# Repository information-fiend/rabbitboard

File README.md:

<h2 align="center">
 
 rabbitboard
</h2>
&nbsp;

> A 65% mechanical keyboard with a knob and screen. 

After making a macropad, holding it felt like *whoa* i wanna make more. Started designing back in March but finished it cuz of Highway! 

### 📷 Pictures

### BOM
|Qty| Device|	Link	|Cost	|
|---|-----|--------|-------|
65|	Through-hole 1N4148 Diodes	|[Link](https://www.aliexpress.us/item/3256807621334582.html?spm=a2g0o.productlist.main.1.50f12c82bUE2UV&algo_pvid=27e25c8f-8c60-43dc-923e-169df02358de&algo_exp_id=27e25c8f-8c60-43dc-923e-169df02358de-0&pdp_ext_f=%7B%22order%22%3A%2298%22%2C%22eval%22%3A%221%22%7D&pdp_npi=4%40dis%21USD%211.29%211.05%21%21%211.29%211.05%21%402101ea8c17508919477924838e28ed%2112000042270438468%21sea%21US%210%21ABX&curPageLogUid=Lgtjbk117rUA&utparam-url=scene%3Asearch%7Cquery_from%3A)|	$1.05
1	|EC11 Rotary encoders	|[Link](https://www.aliexpress.us/item/3256804721655912.html?spm=a2g0o.productlist.main.1.77324f4dhjIsyp&algo_pvid=5a8207c4-5f5f-41b3-8e0e-15b093b58d0f&algo_exp_id=5a8207c4-5f5f-41b3-8e0e-15b093b58d0f-0&pdp_ext_f=%7B%22order%22%3A%22862%22%2C%22eval%22%3A%221%22%7D&pdp_npi=4%40dis%21USD%212.45%212.25%21%21%2117.46%2116.03%21%40210318ec17508936740954018e19d5%2112000035534364746%21sea%21US%210%21ABX&curPageLogUid=d2XXoDwGFi6m&utparam-url=scene%3Asearch%7Cquery_from%3A)|	$3.85
1	|XIAO nRF52840 BLE	|[Link](https://www.amazon.com/Seeed-Studio-XIAO-nRF52840-Microcontroller/dp/B09T9VVQG7?crid=1SL1GXUMI07RW&dib=eyJ2IjoiMSJ9.rHN7uD-Y7j9yR_JnFCk1WQQIaLL3CNzdZH6ZDlRos1R33oxI9P7Zum3B_tfoU2IfHmKvXoYE04WL9ZlO5hTof2PIF6YPhgJ6buA6LhDbAlPMq-6nQ-K1wIXMDdTwV6OQy9xB3HZzvYxMMZ97G81RfgEHvN4Oackki-KO44qbuwbvEHkoRZzrTpoFTUDzc_GKZ--d4_o0F_dq-krODL7oDcaYnK-QX7cHDvqA69QWVgg.QdR6wwFlJCWm_awF7aT7_bLf2xvAXJ4E7VynLmG2mfc&dib_tag=se&keywords=XIAO%2BnRF52840%2BBLE&qid=1750893827&sprefix=xiao%2Bnrf52840%2Bble%2Caps%2C241&sr=8-1&th=1)|	$16.99
64	|Akko V3 Pro Matcha Green Switches|	[Link](https://www.aliexpress.us/item/3256807480638250.html?spm=a2g0o.productlist.main.13.2ee62b10El6MX7&utparam-url=scene%3Asearch%7Cquery_from%3Apc_back_same_best&algo_pvid=60312f2e-eb1f-47c3-9b2c-e78950e5390e&algo_exp_id=60312f2e-eb1f-47c3-9b2c-e78950e5390e&pdp_ext_f=%7B%22order%22%3A%22449%22%7D&pdp_npi=4%40dis%21USD%2124.13%218.78%21%21%21172.00%2162.58%21%402101584917508917311933597ed966%2112000041752524264%21sea%21US%210%21ABX&gatewayAdapt=4itemAdapt)|	$17.56
4	|4.7kΩ resistors|	[Link](https://www.aliexpress.us/item/3256805483786320.html?spm=a2g0o.productlist.main.2.62d6534339SB5P&algo_pvid=54463125-d994-49aa-9bf7-33c766bd2eee&algo_exp_id=54463125-d994-49aa-9bf7-33c766bd2eee-1&pdp_ext_f=%7B%22order%22%3A%222393%22%2C%22eval%22%3A%221%22%7D&pdp_npi=4%40dis%21USD%212.03%210.91%21%21%2114.45%216.44%21%402103273e17508941866188068e601c%2112000033959206034%21sea%21US%210%21ABX&curPageLogUid=YCadnx4DcynD&utparam-url=scene%3Asearch%7Cquery_from%3A)|	$0.94
1	|MCP23017 io expander chip	|[Link](https://www.aliexpress.us/item/3256807880535113.html?spm=a2g0o.productlist.main.1.14e74bd3AMg8My&algo_pvid=fff32110-e2f9-4579-9cd8-07757531a907&algo_exp_id=fff32110-e2f9-4579-9cd8-07757531a907-0&pdp_ext_f=%7B%22order%22%3A%22146%22%2C%22eval%22%3A%221%22%7D&pdp_npi=4%40dis%21USD%213.06%212.76%21%21%213.06%212.76%21%40210313e917508944910767418ed4f8%2112000043519110514%21sea%21US%210%21ABX&curPageLogUid=MlVhdlZkPIfp&utparam-url=scene%3Asearch%7Cquery_from%3A)|	$2.76
1	|0.96 inch OLED 128X64	|[Link](https://www.aliexpress.us/item/3256806315309280.html?spm=a2g0o.productlist.main.1.10367664NY7H92&algo_pvid=5be83edb-d1ee-4df1-81a8-8aa6ed40c05d&algo_exp_id=5be83edb-d1ee-4df1-81a8-8aa6ed40c05d-0&pdp_ext_f=%7B%22order%22%3A%223978%22%2C%22eval%22%3A%221%22%7D&pdp_npi=4%40dis%21USD%212.87%211.55%21%21%2120.49%2111.07%21%402103245417508945281961596e374e%2112000037447041135%21sea%21US%210%21ABX&curPageLogUid=id8EBb4p523v&utparam-url=scene%3Asearch%7Cquery_from%3A#nav-review)|	$1.60
1 set|	Keycaps|	[Link](https://www.amazon.com/HITIME-XVX-Keycaps-Dye-Sublimation-Keyboard/dp/B0D72V6FKM?ref_=ast_sto_dp&th=1)| 	$21.99
6	|Gasket foam strips	|[Link](https://www.aliexpress.us/item/3256806077981729.html?spm=a2g0o.productlist.main.6.76c33f4ei1nFum&algo_pvid=e4a56ac1-3b4b-408f-8513-ffa5748f3fe1&algo_exp_id=e4a56ac1-3b4b-408f-8513-ffa5748f3fe1-5&pdp_ext_f=%7B%22order%22%3A%224%22%2C%22eval%22%3A%221%22%7D&pdp_npi=4%40dis%21USD%215.69%215.49%21%21%215.69%215.49%21%402101c5a417509011156343115e2846%2112000036525961486%21sea%21US%210%21ABX&curPageLogUid=8FyCQlwHz511&utparam-url=scene%3Asearch%7Cquery_from%3A)|	$5.49
2	|Plate-mounted stabilizers|	[Link](https://www.aliexpress.us/item/3256809103980221.html?spm=a2g0o.productlist.main.28.1a2088d5xnKPL7&algo_pvid=e3fefa93-c368-4fcd-a908-8a795415f731&algo_exp_id=e3fefa93-c368-4fcd-a908-8a795415f731-25&pdp_ext_f=%7B%22order%22%3A%221%22%2C%22eval%22%3A%221%22%7D&pdp_npi=4%40dis%21USD%216.64%212.19%21%21%2147.36%2115.62%21%402103010b17508999714684626e7fab%2112000048630570786%21sea%21US%210%21ABX&curPageLogUid=5UCB3dMY8hON&utparam-url=scene%3Asearch%7Cquery_from%3A#nav-review)	|$3.02|
1	|Knob	|[Link](https://www.aliexpress.us/item/3256806828807921.html?spm=a2g0o.productlist.main.27.4926LEfhLEfhij&algo_pvid=13efcc10-3ef6-460a-a95c-08b46874ddc7&algo_exp_id=13efcc10-3ef6-460a-a95c-08b46874ddc7-26&pdp_ext_f=%7B%22order%22%3A%228%22%2C%22eval%22%3A%221%22%7D&pdp_npi=4%40dis%21USD%211.26%210.98%21%21%218.96%216.99%21%402101efeb17508932721343243e8abc%2112000039078414488%21sea%21US%210%21ABX&curPageLogUid=BmdwOHK9lXv3&utparam-url=scene%3Asearch%7Cquery_from%3A)	|$0.99|
1	|PCB|	JLCPCB	|$17.10|
1	|Bottom case	|PCBWay	|$19.80|
1	|Plate	|PCBWay	|$11.61|
1	|Top case	|PCBWay|	$22.96|
|         |   |    | = $147.71

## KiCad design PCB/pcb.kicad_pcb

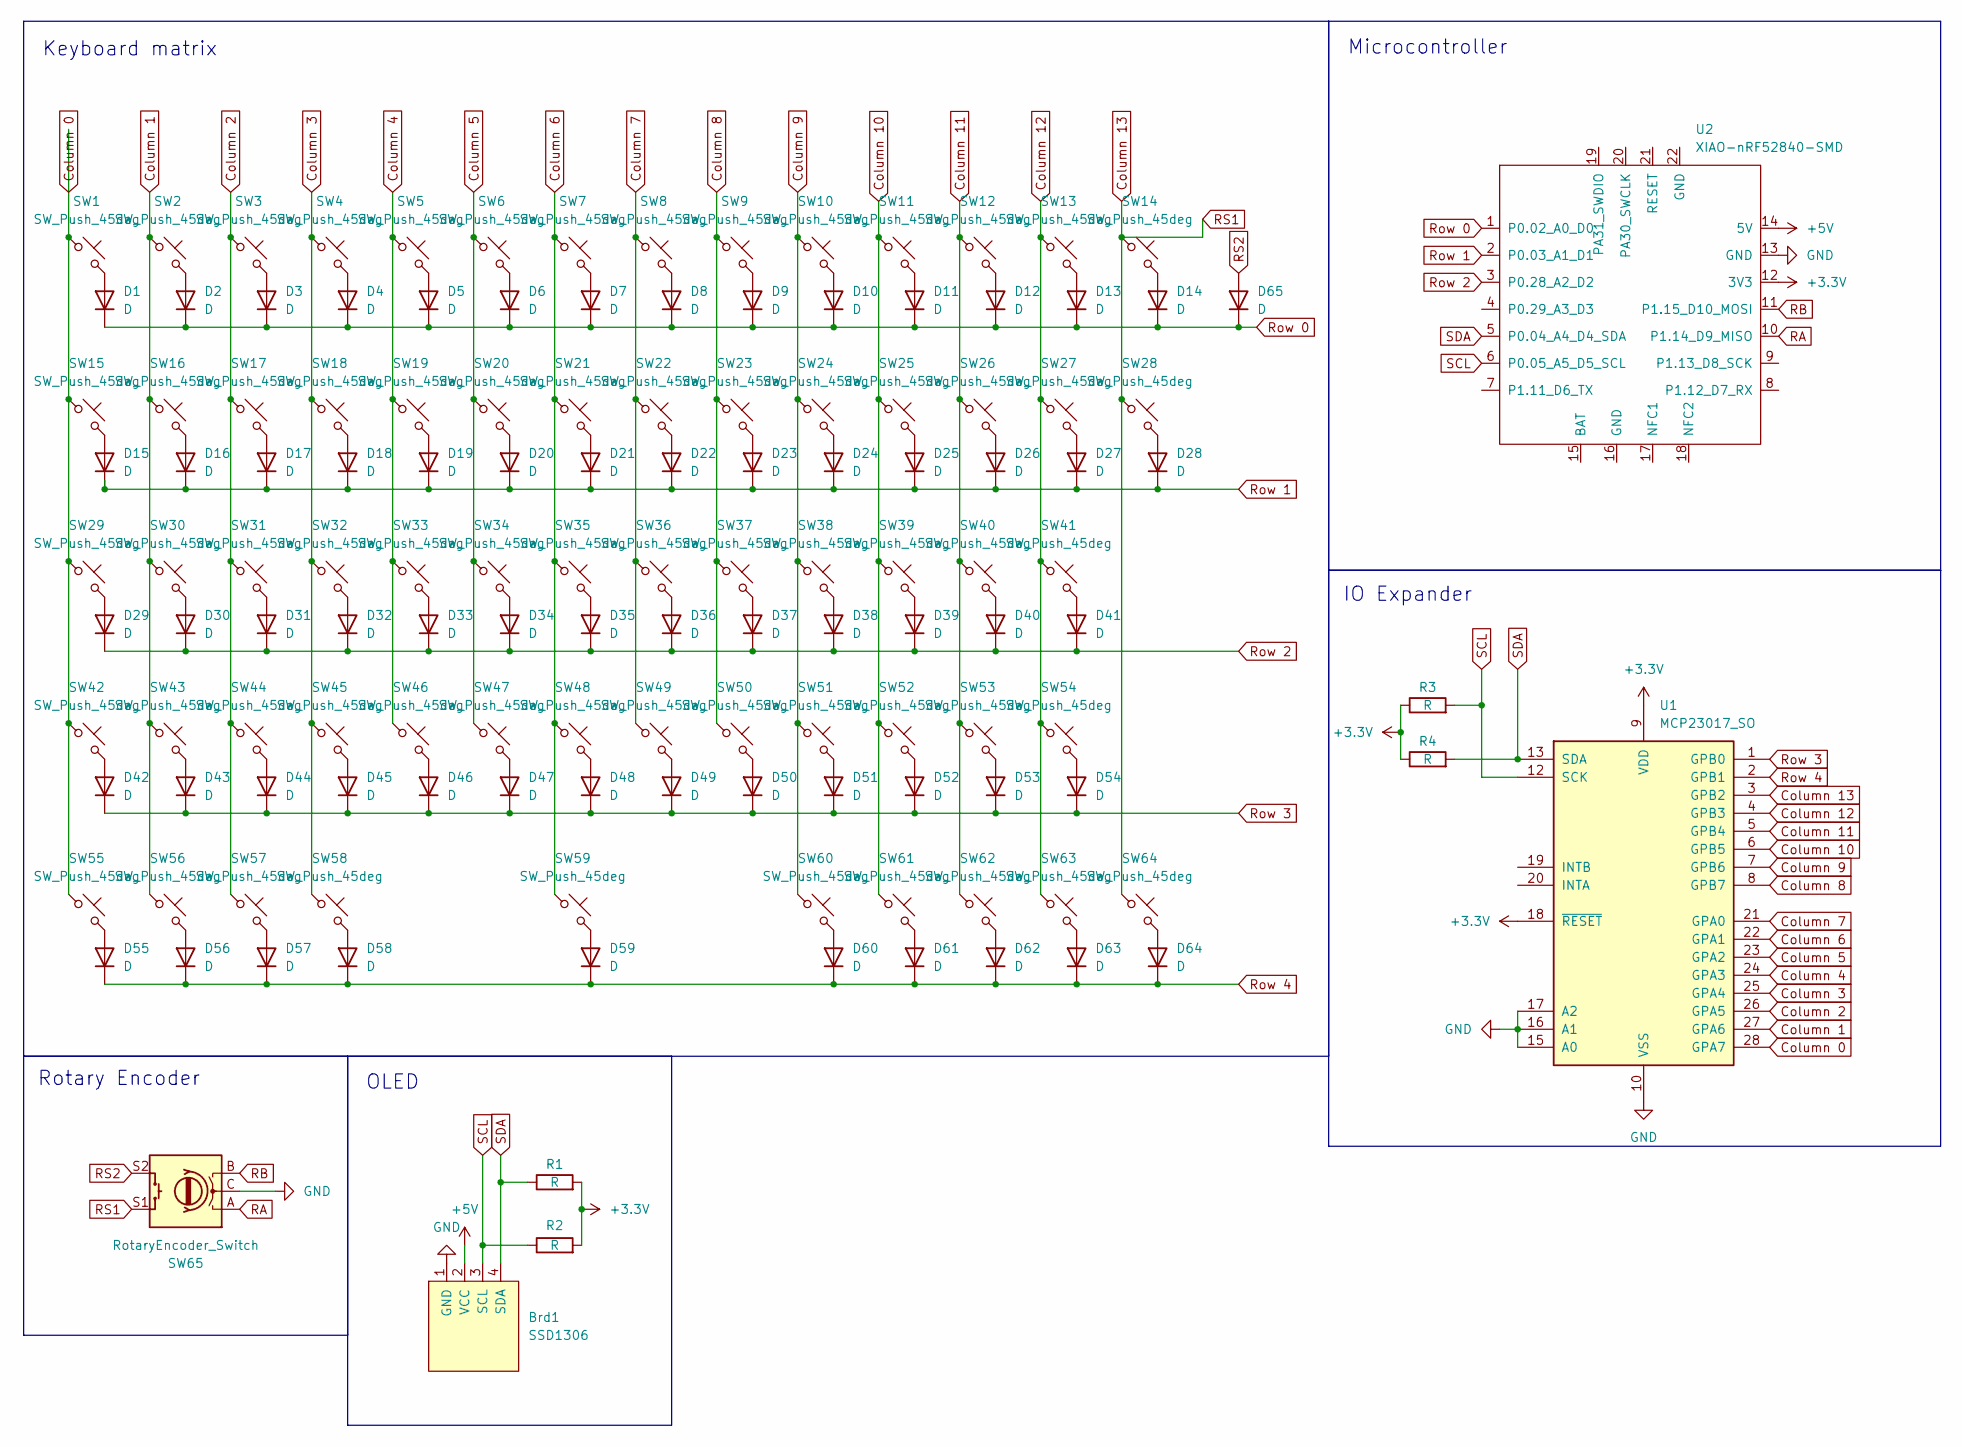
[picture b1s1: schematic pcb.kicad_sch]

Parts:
Brd1: SSD1306; 128x64OLED
D1, D2, D3, D4, D5, D6, D7, D8, D9, D10, D11, D12, D13, D14, D15, D16, D17, D18, D19, D20, D21, D22, D23, D24, D25, D26, D27, D28, D29, D30, D31, D32, D33, D34, D35, D36, D37, D38, D39, D40, D41, D42, D43, D44, D45, D46, D47, D48, D49, D50, D51, D52, D53, D54, D55, D56, D57, D58, D59, D60, D61, D62, D63, D64, D65: D; D_DO-35_SOD27_P7.62mm_Horizontal
R1, R2, R3, R4: R; R_Axial_DIN0204_L3.6mm_D1.6mm_P7.62mm_Horizontal
SW1, SW2, SW3, SW4, SW5, SW6, SW7, SW8, SW9, SW10, SW11, SW12, SW13, SW14, SW15, SW16, SW17, SW18, SW19, SW20, SW21, SW22, SW23, SW24, SW25, SW26, SW27, SW28, SW29, SW30, SW31, SW32, SW33, SW34, SW35, SW36, SW37, SW38, SW39, SW40, SW41, SW42, SW43, SW44, SW45, SW46, SW47, SW48, SW49, SW50, SW51, SW52, SW53, SW54, SW55, SW56, SW57, SW58, SW59, SW60, SW61, SW62, SW63, SW64: SW_Push_45deg; SW_Cherry_MX_1.00u_PCB
SW65: RotaryEncoder_Switch; RotaryEncoder_Alps_EC11E-Switch_Vertical_H20mm_CircularMoun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
U1: MCP23017_SO; SOIC-28W_7.5x17.9mm_P1.27mm
U2: XIAO-nRF52840-SMD

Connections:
+3.3V: R1.2, R2.2, R3.1, R4.1, U1.9 (VDD), U1.18 (~RESET), U2.12 (3V3)
+5V: Brd1.2 (VCC), U2.14 (5V)
Column 0: SW1.1, SW15.1, SW29.1, SW42.1, SW55.1, U1.28 (GPA7)
Column 1: SW2.1, SW16.1, SW30.1, SW43.1, SW56.1, U1.27 (GPA6)
Column 2: SW3.1, SW17.1, SW31.1, SW44.1, SW57.1, U1.26 (GPA5)
Column 3: SW4.1, SW18.1, SW32.1, SW45.1, SW58.1, U1.25 (GPA4)
Column 4: SW5.1, SW19.1, SW33.1, SW46.1, U1.24 (GPA3)
Column 5: SW6.1, SW20.1, SW34.1, SW47.1, U1.23 (GPA2)
Column 6: SW7.1, SW21.1, SW35.1, SW48.1, SW59.1, U1.22 (GPA1)
Column 7: SW8.1, SW22.1, SW36.1, SW49.1, U1.21 (GPA0)
Column 8: SW9.1, SW23.1, SW37.1, SW50.1, U1.8 (GPB7)
Column 9: SW10.1, SW24.1, SW38.1, SW51.1, SW60.1, U1.7 (GPB6)
Column 10: SW11.1, SW25.1, SW39.1, SW52.1, SW61.1, U1.6 (GPB5)
Column 11: SW12.1, SW26.1, SW40.1, SW53.1, SW62.1, U1.5 (GPB4)
Column 12: SW13.1, SW27.1, SW41.1, SW54.1, SW63.1, U1.4 (GPB3)
Column 13: SW14.1, SW28.1, SW64.1, SW65.S1, U1.3 (GPB2)
GND: Brd1.1 (GND), SW65.C, U1.10 (VSS), U1.15 (A0), U1.16 (A1), U1.17 (A2), U2.13 (GND)
unnamed: D1.2 (A), SW1.2
unnamed: D2.2 (A), SW2.2
unnamed: D3.2 (A), SW3.2
unnamed: D4.2 (A), SW4.2
unnamed: D5.2 (A), SW5.2
unnamed: D6.2 (A), SW6.2
unnamed: D7.2 (A), SW7.2
unnamed: D8.2 (A), SW8.2
unnamed: D9.2 (A), SW9.2
unnamed: D10.2 (A), SW10.2
unnamed: D11.2 (A), SW11.2
unnamed: D12.2 (A), SW12.2
unnamed: D13.2 (A), SW13.2
unnamed: D14.2 (A), SW14.2
unnamed: D15.2 (A), SW15.2
unnamed: D16.2 (A), SW16.2
unnamed: D17.2 (A), SW17.2
unnamed: D18.2 (A), SW18.2
unnamed: D19.2 (A), SW19.2
unnamed: D20.2 (A), SW20.2
unnamed: D21.2 (A), SW21.2
unnamed: D22.2 (A), SW22.2
unnamed: D23.2 (A), SW23.2
unnamed: D24.2 (A), SW24.2
unnamed: D25.2 (A), SW25.2
unnamed: D26.2 (A), SW26.2
unnamed: D27.2 (A), SW27.2
unnamed: D28.2 (A), SW28.2
unnamed: D29.2 (A), SW29.2
unnamed: D30.2 (A), SW30.2
unnamed: D31.2 (A), SW31.2
unnamed: D32.2 (A), SW32.2
unnamed: D33.2 (A), SW33.2
unnamed: D34.2 (A), SW34.2
unnamed: D35.2 (A), SW35.2
unnamed: D36.2 (A), SW36.2
unnamed: D37.2 (A), SW37.2
unnamed: D38.2 (A), SW38.2
unnamed: D39.2 (A), SW39.2
unnamed: D40.2 (A), SW40.2
unnamed: D41.2 (A), SW41.2
unnamed: D42.2 (A), SW42.2
unnamed: D43.2 (A), SW43.2
unnamed: D44.2 (A), SW44.2
unnamed: D45.2 (A), SW45.2
unnamed: D46.2 (A), SW46.2
unnamed: D47.2 (A), SW47.2
unnamed: D48.2 (A), SW48.2
unnamed: D49.2 (A), SW49.2
unnamed: D50.2 (A), SW50.2
unnamed: D51.2 (A), SW51.2
unnamed: D52.2 (A), SW52.2
unnamed: D53.2 (A), SW53.2
unnamed: D54.2 (A), SW54.2
unnamed: D55.2 (A), SW55.2
unnamed: D56.2 (A), SW56.2
unnamed: D57.2 (A), SW57.2
unnamed: D58.2 (A), SW58.2
unnamed: D59.2 (A), SW59.2
unnamed: D60.2 (A), SW60.2
unnamed: D61.2 (A), SW61.2
unnamed: D62.2 (A), SW62.2
unnamed: D63.2 (A), SW63.2
unnamed: D64.2 (A), SW64.2
RA: SW65.A, U2.10 (P1.14_D9_MISO)
RB: SW65.B, U2.11 (P1.15_D10_MOSI)
RS2: D65.2 (A), SW65.S2
Row 0: D1.1 (K), D2.1 (K), D3.1 (K), D4.1 (K), D5.1 (K), D6.1 (K), D7.1 (K), D8.1 (K), D9.1 (K), D10.1 (K), D11.1 (K), D12.1 (K), D13.1 (K), D14.1 (K), D65.1 (K), U2.1 (P0.02_A0_D0)
Row 1: D15.1 (K), D16.1 (K), D17.1 (K), D18.1 (K), D19.1 (K), D20.1 (K), D21.1 (K), D22.1 (K), D23.1 (K), D24.1 (K), D25.1 (K), D26.1 (K), D27.1 (K), D28.1 (K), U2.2 (P0.03_A1_D1)
Row 2: D29.1 (K), D30.1 (K), D31.1 (K), D32.1 (K), D33.1 (K), D34.1 (K), D35.1 (K), D36.1 (K), D37.1 (K), D38.1 (K), D39.1 (K), D40.1 (K), D41.1 (K), U2.3 (P0.28_A2_D2)
Row 3: D42.1 (K), D43.1 (K), D44.1 (K), D45.1 (K), D46.1 (K), D47.1 (K), D48.1 (K), D49.1 (K), D50.1 (K), D51.1 (K), D52.1 (K), D53.1 (K), D54.1 (K), U1.1 (GPB0)
Row 4: D55.1 (K), D56.1 (K), D57.1 (K), D58.1 (K), D59.1 (K), D60.1 (K), D61.1 (K), D62.1 (K), D63.1 (K), D64.1 (K), U1.2 (GPB1)
SCL: Brd1.3 (SCL), R2.1, R3.2, U1.12 (SCK), U2.6 (P0.05_A5_D5_SCL)
SDA: Brd1.4 (SDA), R1.1, R4.2, U1.13 (SDA), U2.5 (P0.04_A4_D4_SDA)

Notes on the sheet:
OLED
Keyboard matrix
Rotary Encoder
IO Expander
Microcontroller

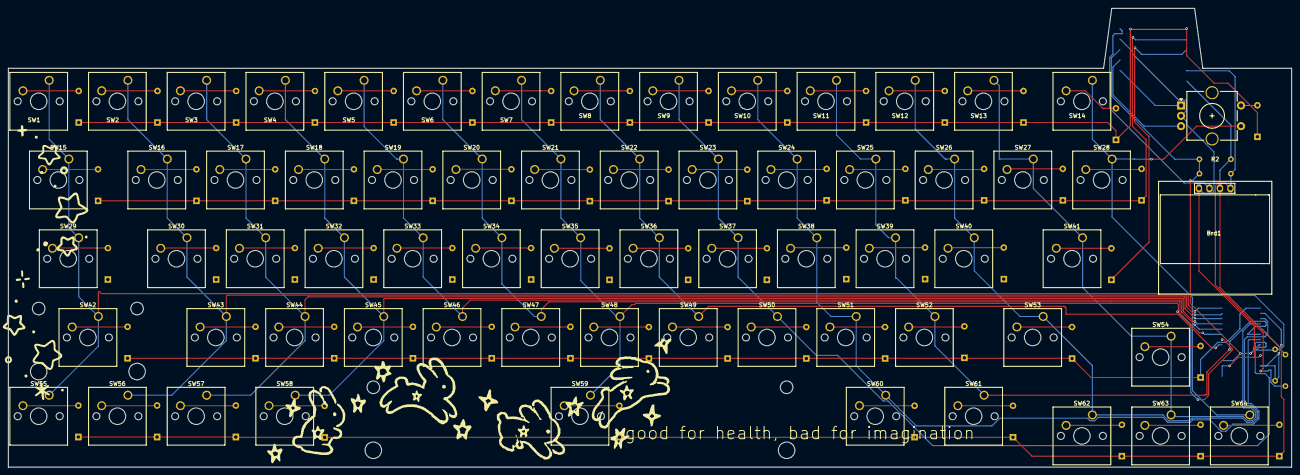
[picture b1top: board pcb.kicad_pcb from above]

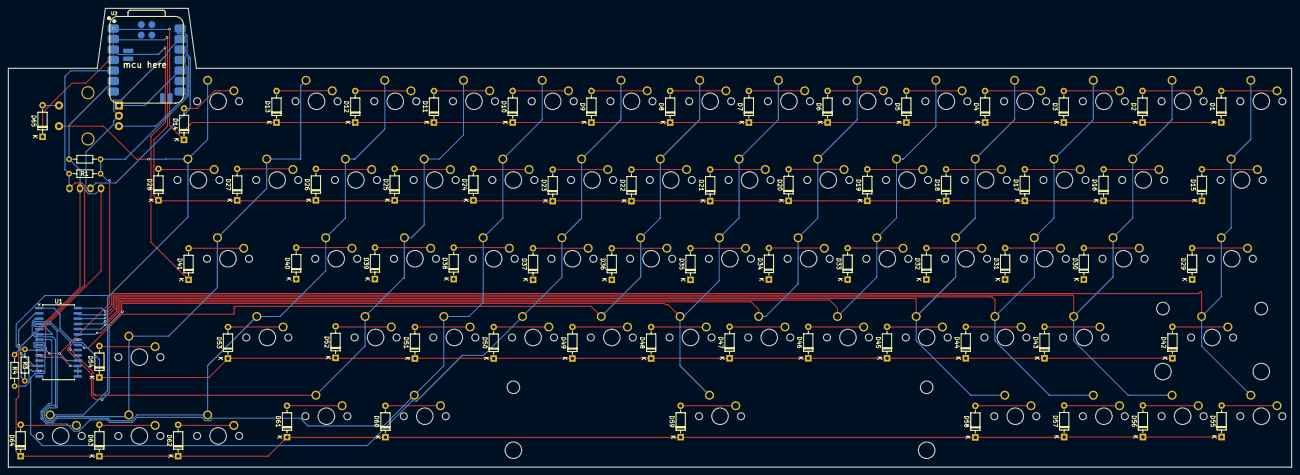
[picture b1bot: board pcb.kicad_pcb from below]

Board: 2 copper layers, 310.5 x 111.0 mm, 137 parts (71 on the bottom side), 91 nets.

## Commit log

2025-05-28 5/27
2025-05-29 5/28 pt1
2025-06-13 6/12
2025-06-19 6/14
2025-06-21 Create hi
2025-06-21 Create hllo
2025-06-21 Create maybe
2025-06-21 pcb :D
2025-06-21 wheee
2025-06-21 6/21
2025-06-24 Create circuitpython
